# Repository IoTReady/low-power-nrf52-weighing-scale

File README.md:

# Smart Weighing Scale  

This project describes a Smart Weighing Scale with low current consumption, and hence a long battery backup.

One of the biggest problems with the use of weighing scales in flexible retail or industrial applications is the need to provide a source of power to a scale. This causes problems such as safety hazards with a corded scale, inflexibility of placement since the location of power sources limits where the scale can be placed, and finally the inability to function when there is a power interruption. This design eliminates these disadvanteges.

## Firmware
After cloning or downloading this repo find the firmware documentation here "weighing_scale_nrf/firmware/bootloader/documentation/index.html".

## Circuit

### Power Supply
The nrf Based Weighing Scale operates on 3.3V, and is powered by a 3.7V Li-ion battery.
We use a p-MOSFET(IRLML6401) for reverse polarity protection, and a LDO(Low Drop Out) Regulator(TPS7A0233PDBV) to get a stable 3.3V output supply.

### Battery Charging
We use a Li-ion/Li-polymer linear battery charger IC(BQ21040) for charging the battery via a micro-USB outlet. The led indicator stops glowing when the battery is fully charged.

### nRF Module

We are using the MDBT42Q nRF52840 based module as our main MCU and BLE module. It is a very low current consuming and high performance module.
It needs a 3.3V power supply, and we are using its internal DC/DC regulator which is set by connecting a 10uH and 18nH inductor at DCC and DEC4 pins as shown here. We also use an external 32.768 kHz external crystal. For programming this module we need a Segger JLink Debugger, which is available as a separate device or one could use an on-board debugger from any of the Nordic Dev-boards like PCA400, etc...
We kept a few GPIOs out for future use or if need to integrate anything else with the weighing scale.

To measure the battery level we use this voltage divider circuit and measure it use the on board ADC pins.

Tare Button is a push button for using the tare functionality. It basically resets the displayed weight on scale back to zero. The Tare button can also be used to measure multiple items in the same container. Simply add you first item, note the weight, press Tare and you are ready to weigh your next item.

### ADC Circuit: HX711

For measuring the weighing scale we use a Load Cell which gives an anlog output, as the weight changes. For high accuracy we use HX711 24-bit ADC chip, which is designed specifically for industrial weighing scales and other industrial control applications.

To power the HX711 we need a 5V supply, so we use a Boost regulator(LM2703) to step-up the 3.7V from the battery supply and use an LDO(LP2985-5.0) to get a stable noise free 5V supply for HX711.

The data from the Load Cell is received via four pins HX711_IN+, HX711_IN-, HX711_AVDD and GND. This data is processed by the ADC chip and an output is send via serial interface to the nRF module. We can control the output data rate as either 10Hz or 80Hz by controlling the HX711_RATE pin state.
There is no programming needed for the internal registers. All controls to the HX711 are through the pins.

### E-Ink Display

We decided to go with an E-Ink display as it is very low power consuming, reflection resistant, and was useful for the application we were targeting.
This is a 1.54" 200x200 pixel [E-Ink display](https://www.e-paper-display.com/products_detail/productId=513.html) from Good Display.

## PCB
This is what the final PCB design looks like:

## Hardware Builds

Hardware design files are available in the "design" sub-folder

We tried 3 different designs for the weighing scale project and settled with the "HX711" based design as our final.

So you will find the final design explained on the main page.

The other two designs of "LPV821" and "LTC6915" based weighing scales are also fully functional, one may have to play around with the adc functions in the firmware though.

## Software Builds

One can find the main application with all library files(for e-ink display, and weighing scale) in the "Application" folder.

To setup the Nordic SDK and bootloader files follow the links in "Bootloader" folder. Also, the "documentation" folder has some good technical data.

To make changes in the firmware go to "weighing_scale_nrf/firmware/application/w_scale_all/" and make necessary changes.

To build the output files, go to the same location and use this command to generate final output files(.hex):
```
make release
```

Then use the following to flash and debug the firmware:
```
make upload
```

This is a custom makefile, so make sure all Debugger setings are proper. Like, make sure the Debugge name and Serial Number are correct.

These can be set in this [makefile](https://github.com/IoTReady/weighing_scale_nrf/blob/master/firmware/application/w_scale_all/Makefile).

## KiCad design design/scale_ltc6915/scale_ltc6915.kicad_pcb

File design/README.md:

Here one can find all the Hardware design files.
We tried 3 different designs for the weighing scale project and settled with the "HX711" based design as our final.
So you will find the final design explained on the main page.
The other two designs of "LPV821" and "LTC6915" based weighing scales are also fully functional, one may have to play around with the adc functions in the firmware though.

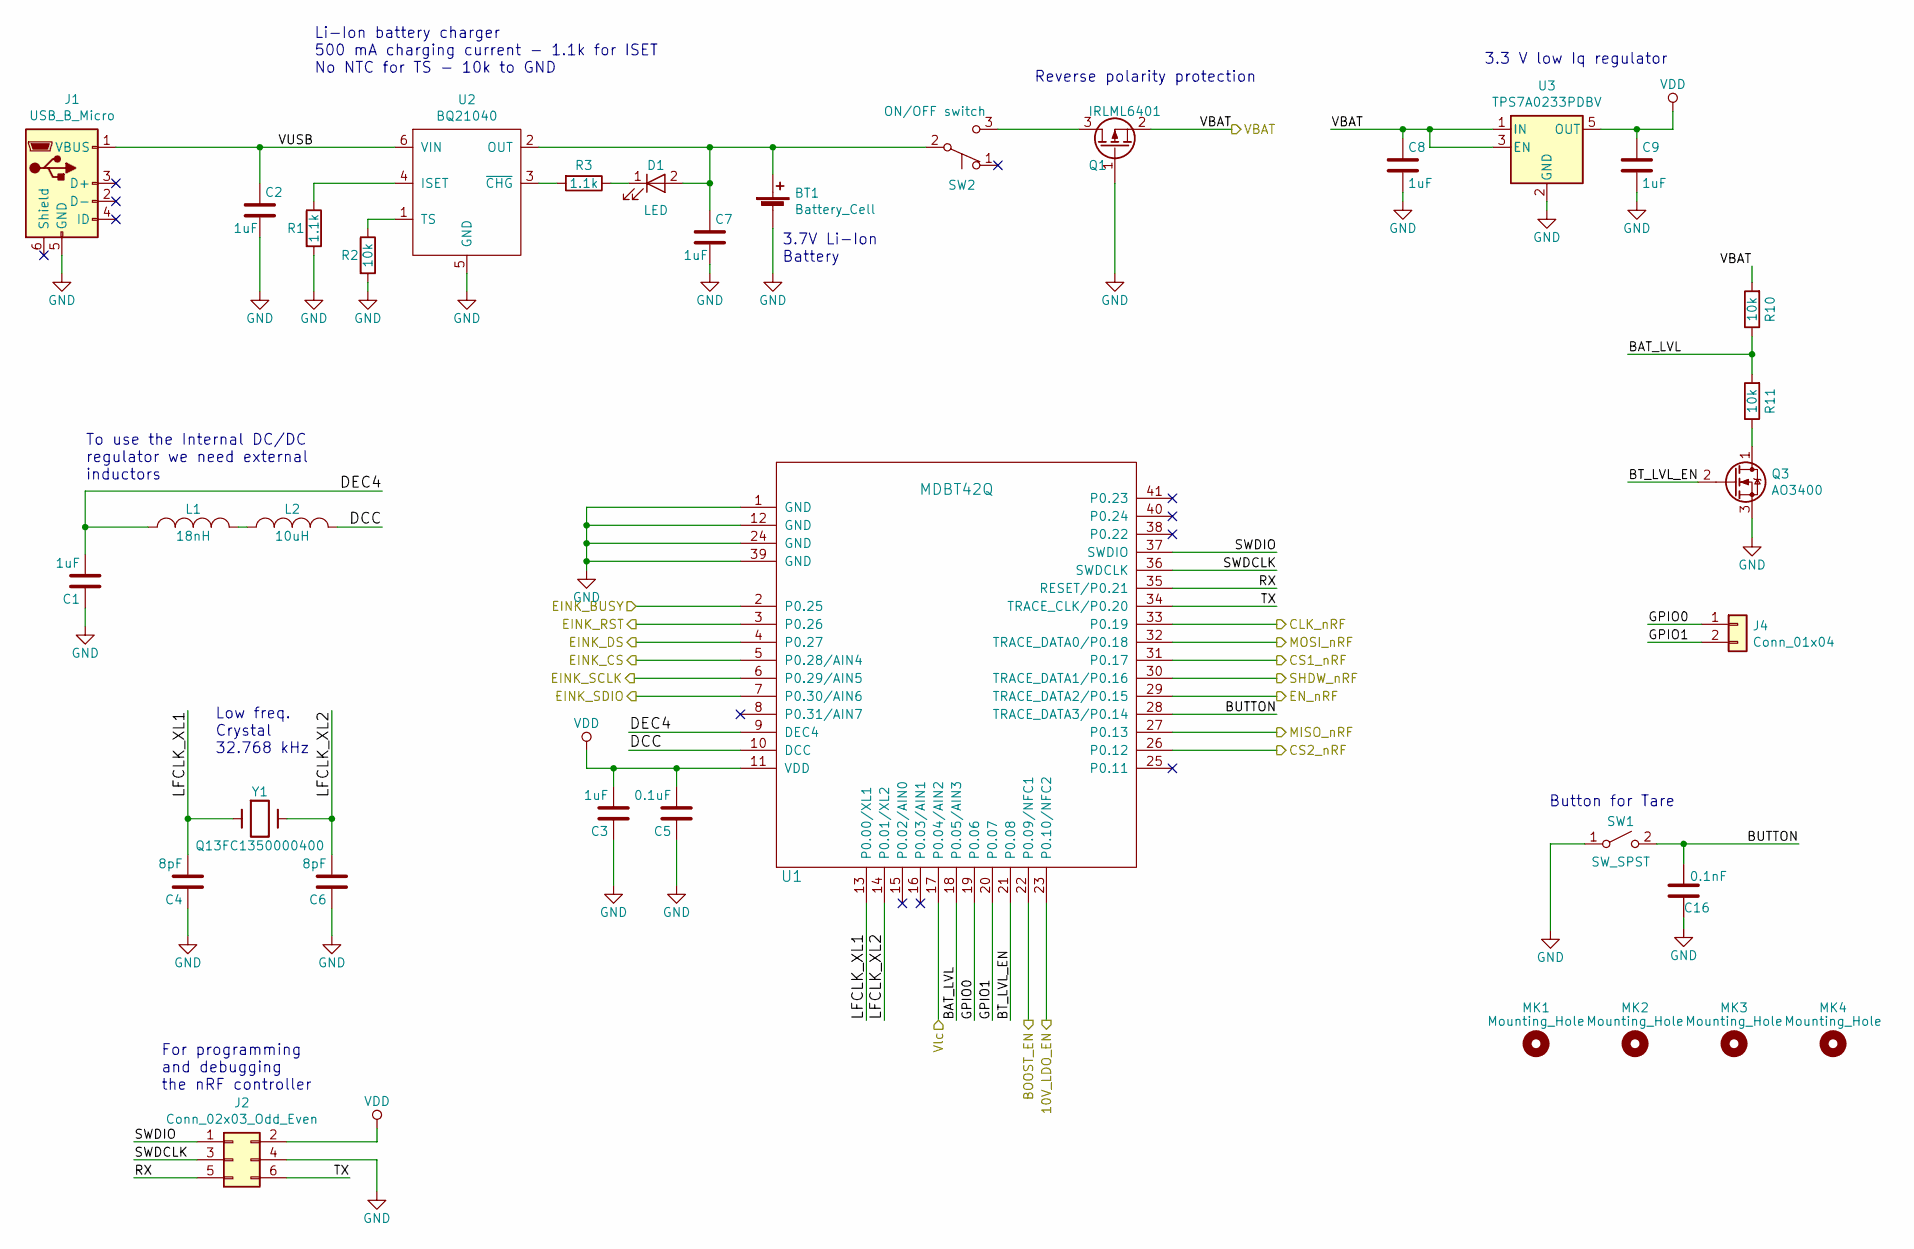
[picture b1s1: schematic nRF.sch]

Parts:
BT1: Battery_Cell; JST_PH_B2B-PH-K_1x02_P2.00mm_Vertical
C1, C3: 1uF; C_0603_1608Metric
C2, C7, C8, C9: 1uF; C_1206_3216Metric
C4, C6: 8pF; C_0402_1005Metric
C5: 0.1uF; C_0402_1005Metric
C16: 0.1nF; C_0402_1005Metric
D1: LED; LED_0603_1608Metric_Castellated
J1: USB_B_Micro; Micro_usb_connector_4_THT_pads
J2: Conn_02x03_Odd_Even; PinHeader_2x03_P2.00mm_Vertical
J4: Conn_01x04; PinHeader_1x02_P2.00mm_Vertical
L1: 18nH; C_0603_1608Metric
L2: 10uH; L_0805
MK1, MK2, MK3, MK4: Mounting_Hole; MountingHole_2.7mm_M2.5
Q1: IRLML6401; SOT-23
Q3: AO3400; SOT-23
R1, R3: 1.1k; R_0603_1608Metric_Pad1.05x0.95mm_HandSolder
R2, R10, R11: 10k; R_0603_1608Metric_Pad1.05x0.95mm_HandSolder
SW1: SW_SPST; SMD Tactile Switch_3x6x2.5mm
SW2: ON/OFF switch; Slide Switch SMD 2P2T _6pins
U1: MDBT42Q; mdbt42Q
U2: BQ21040; SOT-23-6_Handsoldering
U3: TPS7A0233PDBV; SOT-23-5
Y1: Q13FC1350000400; Q13FC1350000400_SMD Crystals 32.768KHz

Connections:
/Sheet5E60241E/EINK_BUSY: U1.2 (P0.25); also elsewhere on the board
/Sheet5E60241E/EINK_CS: U1.5 (P0.28/AIN4); also elsewhere on the board
/Sheet5E60241E/EINK_DS: U1.4 (P0.27); also elsewhere on the board
/Sheet5E60241E/EINK_RST: U1.3 (P0.26); also elsewhere on the board
/Sheet5E60241E/EINK_SCLK: U1.6 (P0.29/AIN5); also elsewhere on the board
/Sheet5E60241E/EINK_SDIO: U1.7 (P0.30/AIN6); also elsewhere on the board
/Sheet5E602498/10V_LDO_EN: U1.23 (P0.10/NFC2); also elsewhere on the board
/Sheet5E602498/BOOST_EN: U1.22 (P0.09/NFC1); also elsewhere on the board
/Sheet5E602498/CLK_nRF: U1.33 (P0.19); also elsewhere on the board
/Sheet5E602498/CS1_nRF: U1.31 (P0.17); also elsewhere on the board
/Sheet5E602498/CS2_nRF: U1.26 (P0.12); also elsewhere on the board
/Sheet5E602498/EN_nRF: U1.29 (TRACE_DATA2/P0.15); also elsewhere on the board
/Sheet5E602498/MISO_nRF: U1.27 (P0.13); also elsewhere on the board
/Sheet5E602498/MOSI_nRF: U1.32 (TRACE_DATA0/P0.18); also elsewhere on the board
/Sheet5E602498/SHDW_nRF: U1.30 (TRACE_DATA1/P0.16); also elsewhere on the board
/Sheet5E602498/VBAT: C8.1, Q1.2 (G), R10.2, U3.1 (IN), U3.3 (EN); also elsewhere on the board
/Sheet5E602498/Vlc: U1.17 (P0.04/AIN2); also elsewhere on the board
/nRF/BAT_LVL: R10.1, R11.2, U1.18 (P0.05/AIN3)
/nRF/BT_LVL_EN: Q3.2 (G), U1.21 (P0.08)
/nRF/BUTTON: C16.2, SW1.2 (B), U1.28 (TRACE_DATA3/P0.14)
/nRF/DCC: L2.2, U1.10 (DCC)
/nRF/DEC4: C1.2, L1.1, U1.9 (DEC4)
/nRF/GPIO0: J4.1, U1.19 (P0.06)
/nRF/GPIO1: J4.2, U1.20 (P0.07)
/nRF/LFCLK_XL1: C4.2, U1.13 (P0.00/XL1), Y1.1
/nRF/LFCLK_XL2: C6.2, U1.14 (P0.01/XL2), Y1.2
/nRF/RX: J2.5, U1.35 (RESET/P0.21)
/nRF/SWDCLK: J2.3, U1.36 (SWDCLK)
/nRF/SWDIO: J2.1, U1.37 (SWDIO)
/nRF/TX: J2.6, U1.34 (TRACE_CLK/P0.20)
/nRF/VUSB: C2.1, J1.1 (VBUS), U2.6 (VIN)
GND: BT1.2, C1.1, C2.2, C3.1, C4.1, C5.1, C6.1, C7.2, C8.2, C9.2, C16.1, J1.5 (GND), J2.4, Q1.1 (D), Q3.3 (S), R1.2, R2.2, SW1.1 (A), U1.1 (GND), U1.12 (GND), U1.24 (GND), U1.39 (GND), U2.5 (GND), U3.2 (GND); also elsewhere on the board
unnamed: BT1.1, C7.1, D1.2 (A), SW2.2 (B), U2.2 (OUT)
unnamed: D1.1 (K), R3.1
unnamed: L1.2, L2.1
unnamed: Q1.3 (S), SW2.3 (C)
unnamed: Q3.1 (D), R11.1
unnamed: R1.1, U2.4 (ISET)
unnamed: R2.1, U2.1 (TS)
unnamed: R3.2, U2.3 (~CHG)
VDD: C3.2, C5.2, C9.1, J2.2, U1.11 (VDD), U3.5 (OUT); also elsewhere on the board

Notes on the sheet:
3.7V Li-Ion Battery
Reverse polarity protection
Button for Tare
To use the Internal DC/DC regulator we need external inductors
For programming and debugging the nRF controller
Low freq. Crystal 32.768 kHz
3.3 V low Iq regulator
Li-Ion battery charger 500 mA charging current - 1.1k for ISET No NTC for TS - 10k to GND

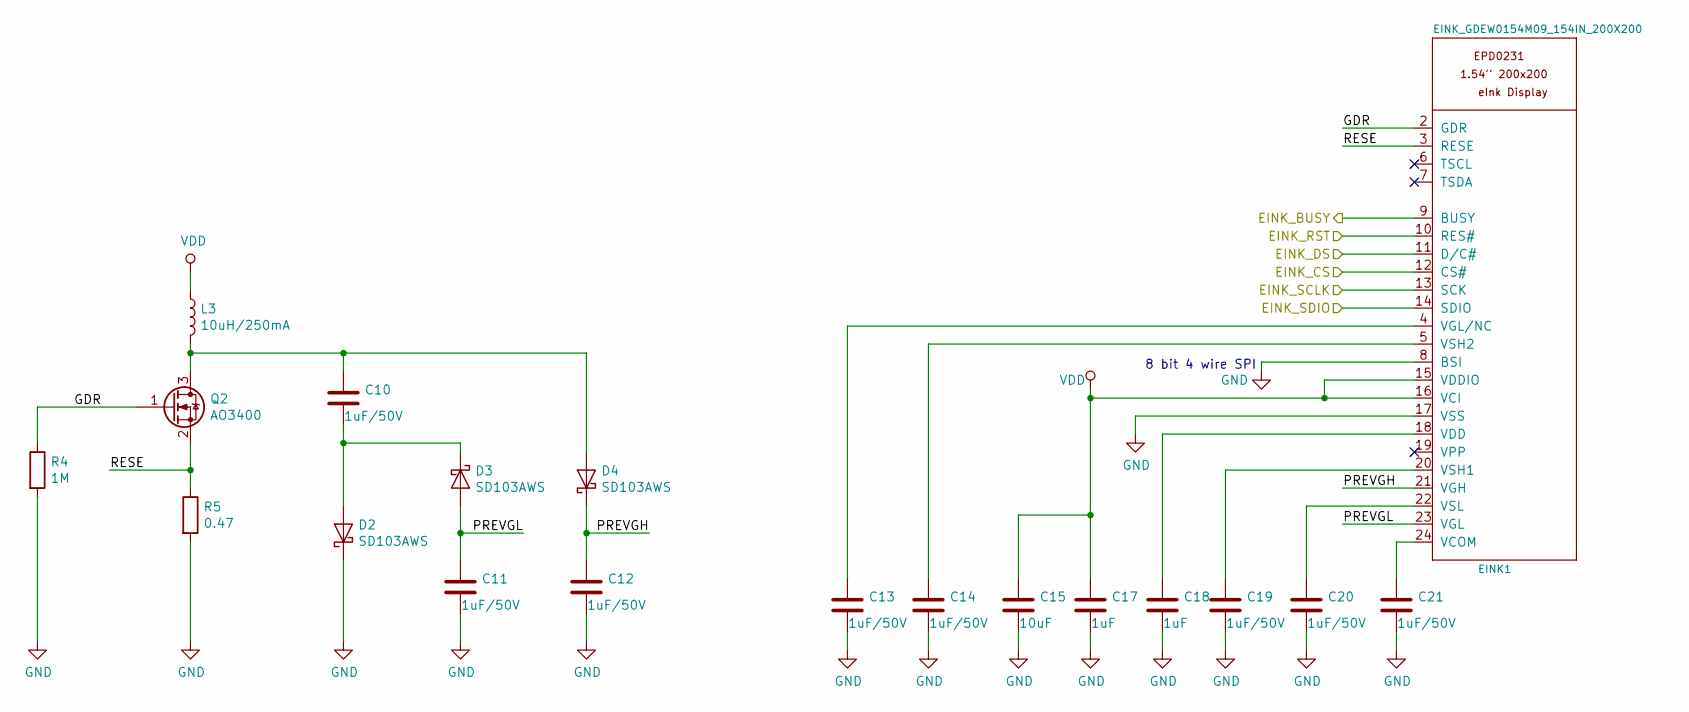
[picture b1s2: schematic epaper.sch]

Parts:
C10, C11, C12, C13, C14, C19, C20, C21: 1uF/50V; C_0603_1608Metric_Pad1.05x0.95mm_HandSolder
C15: 10uF; C_0603_1608Metric_Pad1.05x0.95mm_HandSolder
C17, C18: 1uF; C_0603_1608Metric_Pad1.05x0.95mm_HandSolder
D2, D3, D4: SD103AWS; D_SOD-323_HandSoldering
EINK1: EINK_GDEW0154M09_154IN_200X200; Hirose_FH12-24S-0.5SH_1x24-1MP_P0.50mm_Horizontal
L3: 10uH/250mA; L_3.5x3.0mm_CD30D22
Q2: AO3400; SOT-23
R4: 1M; R_0603_1608Metric_Pad1.05x0.95mm_HandSolder
R5: 0.47; R_1206_3216Metric

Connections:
/Sheet5E60241E/EINK_BUSY: EINK1.9 (BUSY); also elsewhere on the board
/Sheet5E60241E/EINK_CS: EINK1.12 (CS#); also elsewhere on the board
/Sheet5E60241E/EINK_DS: EINK1.11 (D/C#); also elsewhere on the board
/Sheet5E60241E/EINK_RST: EINK1.10 (RES#); also elsewhere on the board
/Sheet5E60241E/EINK_SCLK: EINK1.13 (SCK); also elsewhere on the board
/Sheet5E60241E/EINK_SDIO: EINK1.14 (SDIO); also elsewhere on the board
/Sheet5E60241E/GDR: EINK1.2 (GDR), Q2.1 (G), R4.1
/Sheet5E60241E/PREVGH: C12.1, D4.1 (K), EINK1.21 (VGH)
/Sheet5E60241E/PREVGL: C11.1, D3.2 (A), EINK1.23 (VGL)
/Sheet5E60241E/RESE: EINK1.3 (RESE), Q2.2 (S), R5.1
GND: C11.2, C12.2, C13.2, C14.2, C15.2, C17.2, C18.2, C19.2, C20.2, C21.2, D2.1 (K), EINK1.8 (BSI), EINK1.17 (VSS), R4.2, R5.2; also elsewhere on the board
unnamed: C10.1, D4.2 (A), L3.2, Q2.3 (D)
unnamed: C10.2, D2.2 (A), D3.1 (K)
unnamed: C13.1, EINK1.4 (VGL/NC)
unnamed: C14.1, EINK1.5 (VSH2)
unnamed: C18.1, EINK1.18 (VDD)
unnamed: C19.1, EINK1.20 (VSH1)
unnamed: C20.1, EINK1.22 (VSL)
unnamed: C21.1, EINK1.24 (VCOM)
VDD: C15.1, C17.1, EINK1.15 (VDDIO), EINK1.16 (VCI), L3.1; also elsewhere on the board

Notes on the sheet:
8 bit 4 wire SPI

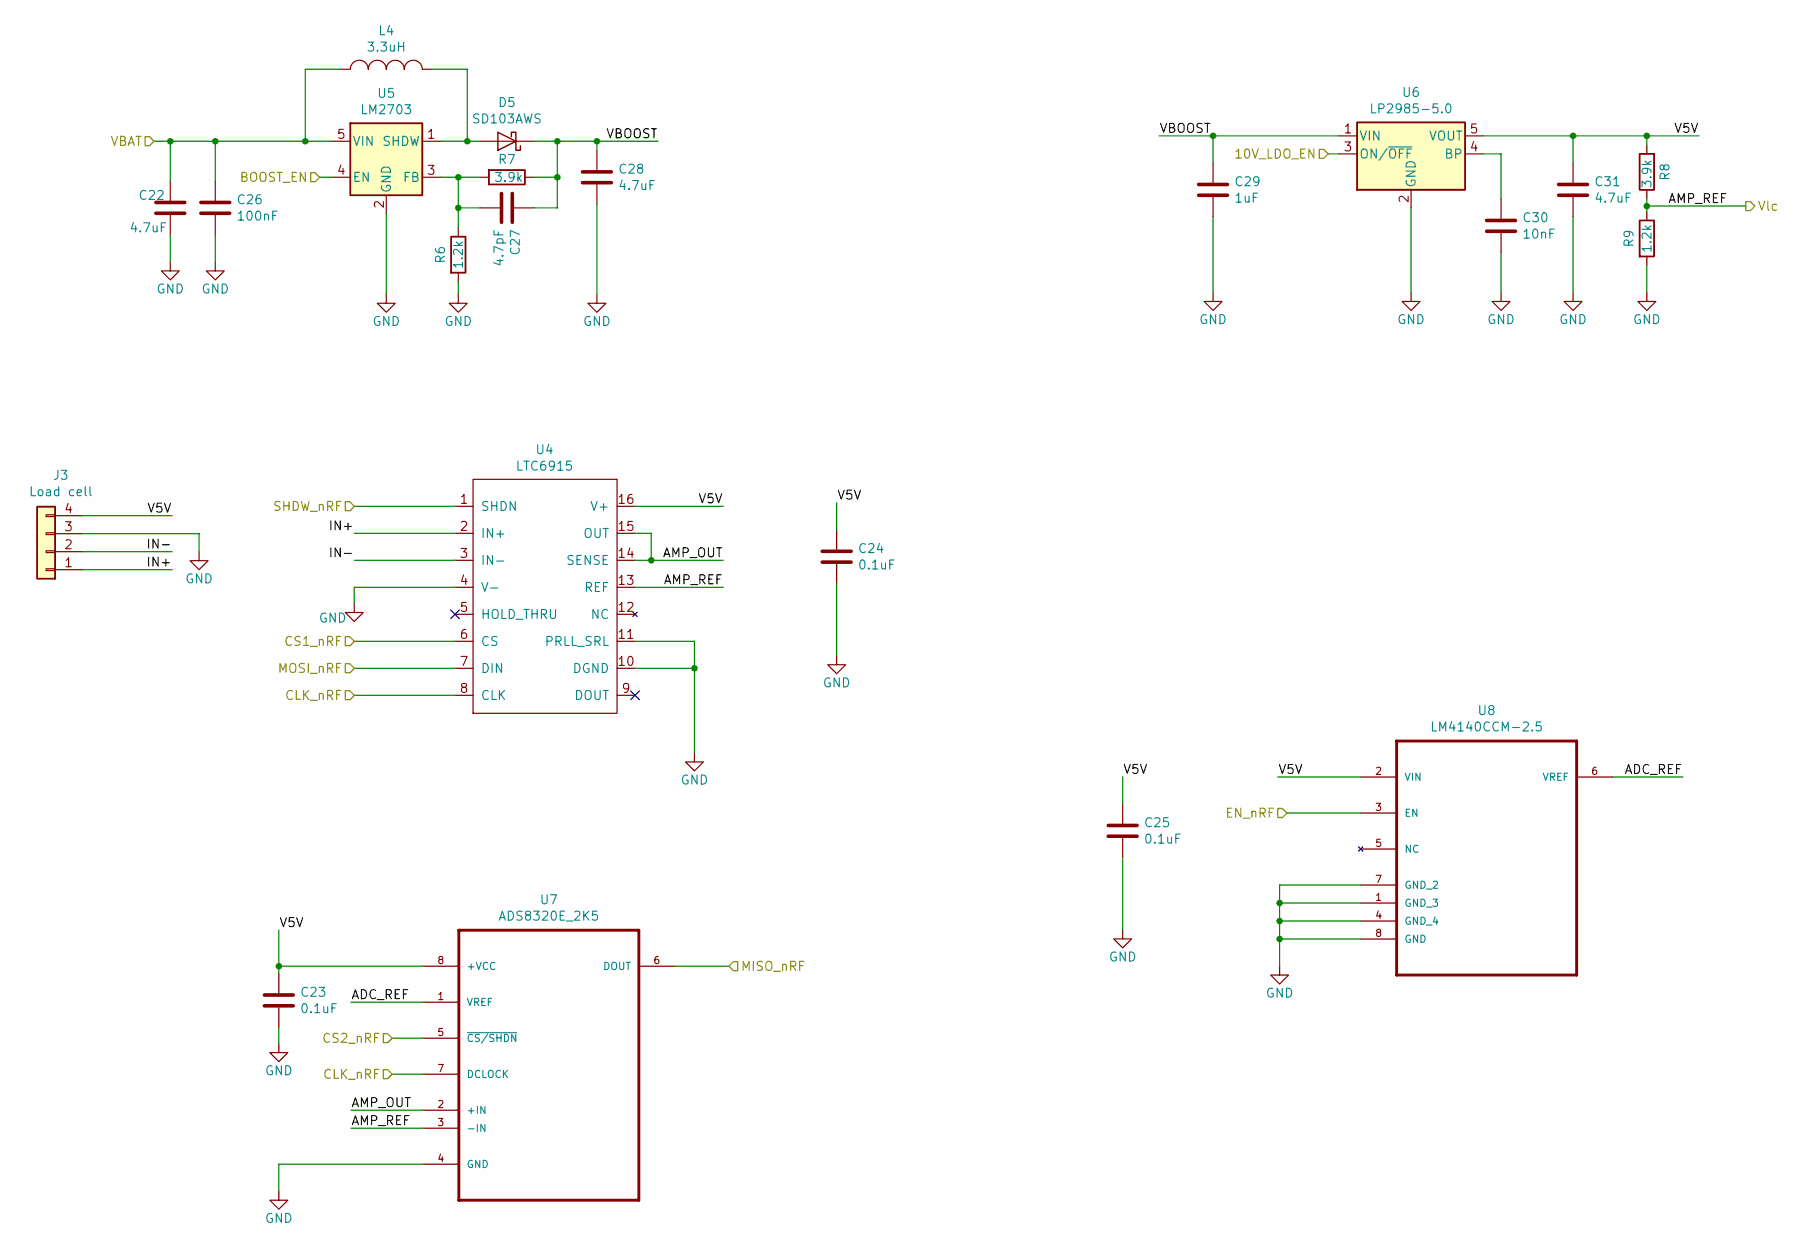
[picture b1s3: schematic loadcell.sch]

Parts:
C22, C28, C31: 4.7uF; C_0603_1608Metric_Pad1.05x0.95mm_HandSolder
C23, C24, C25: 0.1uF; C_0603_1608Metric_Pad1.05x0.95mm_HandSolder
C26: 100nF; C_0603_1608Metric_Pad1.05x0.95mm_HandSolder
C27: 4.7pF; C_0603_1608Metric_Pad1.05x0.95mm_HandSolder
C29: 1uF; C_0603_1608Metric_Pad1.05x0.95mm_HandSolder
C30: 10nF; C_0603_1608Metric_Pad1.05x0.95mm_HandSolder
D5: SD103AWS; D_SOD-323_HandSoldering
J3: Load cell; JST_PH_B4B-PH-K_1x04_P2.00mm_Vertical
L4: 3.3uH; L_3.5x3.0mm_CD30D22
R6, R9: 1.2k; R_0603_1608Metric_Pad1.05x0.95mm_HandSolder
R7, R8: 3.9k; R_0603_1608Metric_Pad1.05x0.95mm_HandSolder
U4: LTC6915; SSOP-16_3.9x4.9mm_P0.635mm
U5: LM2703; SOT-23-5
U6: LP2985-5.0; SOT-23-5
U7: ADS8320E_2K5; VSSOP-8_3.0x3.0mm_P0.65mm
U8: LM4140CCM-2.5; SOIC-8_3.9x4.9mm_P1.27mm

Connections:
/Sheet5E602498/10V_LDO_EN: U6.3 (ON/~OFF~); also elsewhere on the board
/Sheet5E602498/ADC_REF: U7.1 (VREF), U8.6 (VREF)
/Sheet5E602498/AMP_OUT: U4.14 (SENSE), U4.15 (OUT), U7.2 (+IN)
/Sheet5E602498/BOOST_EN: U5.4 (EN); also elsewhere on the board
/Sheet5E602498/CLK_nRF: U4.8 (CLK), U7.7 (DCLOCK); also elsewhere on the board
/Sheet5E602498/CS1_nRF: U4.6 (CS); also elsewhere on the board
/Sheet5E602498/CS2_nRF: U7.5 (~CS/SHDN); also elsewhere on the board
/Sheet5E602498/EN_nRF: U8.3 (EN); also elsewhere on the board
/Sheet5E602498/IN+: J3.1, U4.2 (IN+)
/Sheet5E602498/IN-: J3.2, U4.3 (IN-)
/Sheet5E602498/MISO_nRF: U7.6 (DOUT); also elsewhere on the board
/Sheet5E602498/MOSI_nRF: U4.7 (DIN); also elsewhere on the board
/Sheet5E602498/SHDW_nRF: U4.1 (SHDN); also elsewhere on the board
/Sheet5E602498/V5V: C23.1, C24.1, C25.1, C31.1, J3.4, R8.2, U4.16 (V+), U6.5 (VOUT), U7.8 (+VCC), U8.2 (VIN)
/Sheet5E602498/VBAT: C22.1, C26.1, L4.1, U5.5 (VIN); also elsewhere on the board
/Sheet5E602498/VBOOST: C27.1, C28.1, C29.1, D5.1 (K), R7.1, U6.1 (VIN)
/Sheet5E602498/Vlc: R8.1, R9.1, U4.13 (REF), U7.3 (-IN); also elsewhere on the board
GND: C22.2, C23.2, C24.2, C25.2, C26.2, C28.2, C29.2, C30.2, C31.2, J3.3, R6.2, R9.2, U4.4 (V-), U4.10 (DGND), U4.11 (PRLL_SRL), U5.2 (GND), U6.2 (GND), U7.4 (GND), U8.1 (GND_3), U8.4 (GND_4), U8.7 (GND_2), U8.8 (GND); also elsewhere on the board
unnamed: C27.2, R6.1, R7.2, U5.3 (FB)
unnamed: C30.1, U6.4 (BP)
unnamed: D5.2 (A), L4.2, U5.1 (SHDW)

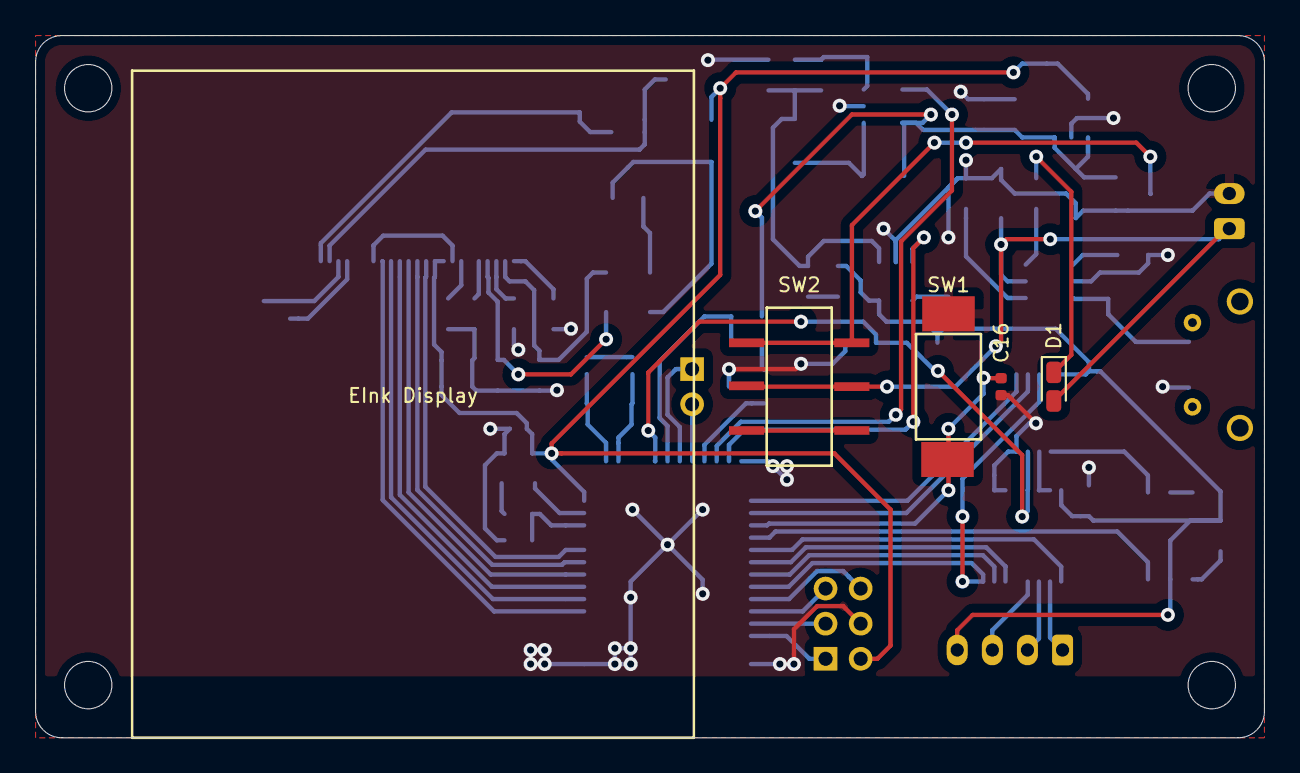
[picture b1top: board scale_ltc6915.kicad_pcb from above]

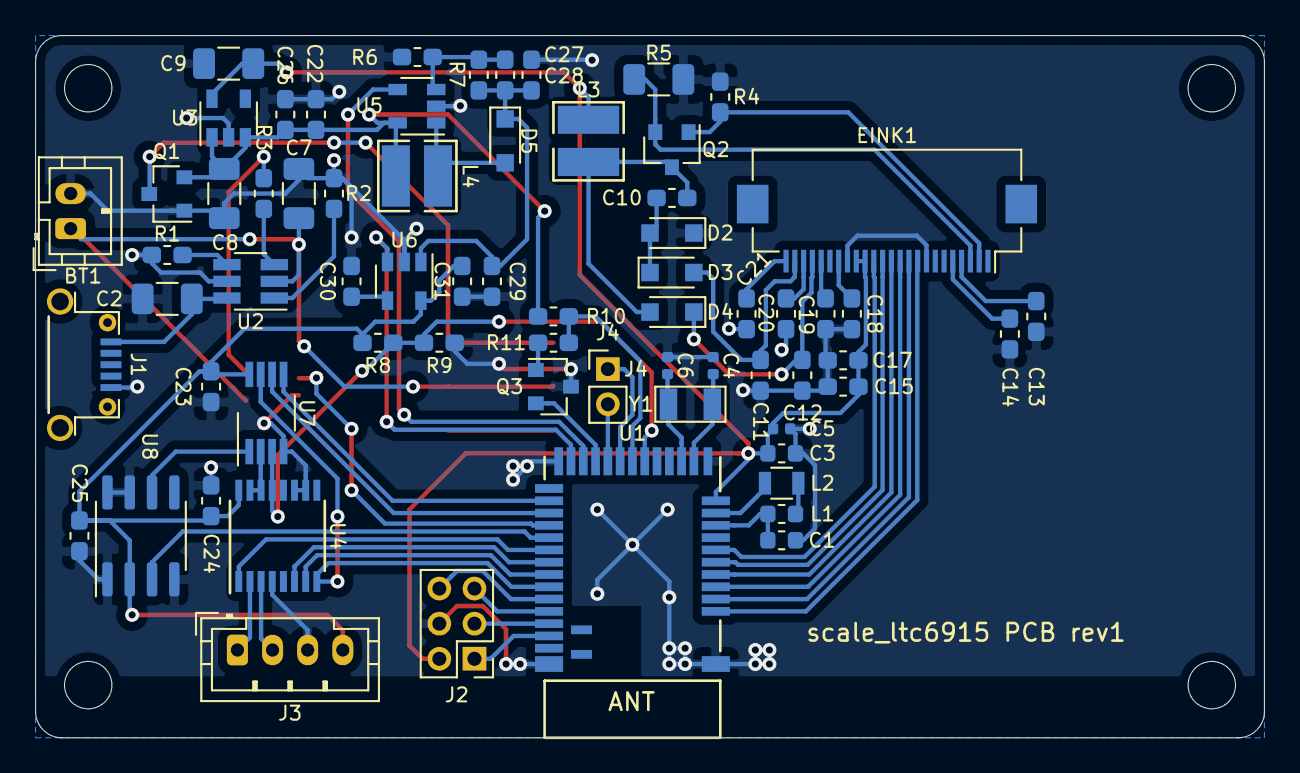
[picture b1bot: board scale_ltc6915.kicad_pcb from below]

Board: 2 copper layers, 70.0 x 40.0 mm, 76 parts (67 on the bottom side), 62 nets.

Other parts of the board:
EInk Display: 1.54inch_EInk_display

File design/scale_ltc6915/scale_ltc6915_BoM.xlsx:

Source: | /home/shubham/IoTReady/nrf_scale/weighing_scale_nrf/design/scale_ltc6915/scale_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
Date: | Fri Mar 6 21:35:52 2020
Tool: | Eeschema 5.1.5-52549c5~84~ubuntu18.04.1
Component Count: | 73
Ref | Value | Footprint | Datasheet | Manufacturer | Vendor
BT1 | Battery_Cell | Connector_JST:JST_PH_B2B-PH-K_1x02_P2.00mm_Vertical
C1 | 1uF | sense_fp:C_0603_1608Metric
C2 | 1uF | sense_fp:C_1206_3216Metric
C3 | 1uF | sense_fp:C_0603_1608Metric
C4 | 8pF | sense_fp:C_0402_1005Metric
C5 | 0.1uF | sense_fp:C_0402_1005Metric
C6 | 8pF | sense_fp:C_0402_1005Metric
C7 | 1uF | sense_fp:C_1206_3216Metric
C8 | 1uF | sense_fp:C_1206_3216Metric
C9 | 1uF | sense_fp:C_1206_3216Metric
C10 | 1uF/50V | Capacitor_SMD:C_0603_1608Metric_Pad1.05x0.95mm_HandSolder
C11 | 1uF/50V | Capacitor_SMD:C_0603_1608Metric_Pad1.05x0.95mm_HandSolder
C12 | 1uF/50V | Capacitor_SMD:C_0603_1608Metric_Pad1.05x0.95mm_HandSolder
C13 | 1uF/50V | Capacitor_SMD:C_0603_1608Metric_Pad1.05x0.95mm_HandSolder
C14 | 1uF/50V | Capacitor_SMD:C_0603_1608Metric_Pad1.05x0.95mm_HandSolder
C15 | 10uF | Capacitor_SMD:C_0603_1608Metric_Pad1.05x0.95mm_HandSolder
C16 | 0.1nF | sense_fp:C_0402_1005Metric
C17 | 1uF | Capacitor_SMD:C_0603_1608Metric_Pad1.05x0.95mm_HandSolder
C18 | 1uF | Capacitor_SMD:C_0603_1608Metric_Pad1.05x0.95mm_HandSolder
C19 | 1uF/50V | Capacitor_SMD:C_0603_1608Metric_Pad1.05x0.95mm_HandSolder
C20 | 1uF/50V | Capacitor_SMD:C_0603_1608Metric_Pad1.05x0.95mm_HandSolder
C21 | 1uF/50V | Capacitor_SMD:C_0603_1608Metric_Pad1.05x0.95mm_HandSolder
C22 | 4.7uF | Capacitor_SMD:C_0603_1608Metric_Pad1.05x0.95mm_HandSolder | ~
C23 | 0.1uF | Capacitor_SMD:C_0603_1608Metric_Pad1.05x0.95mm_HandSolder | ~
C24 | 0.1uF | Capacitor_SMD:C_0603_1608Metric_Pad1.05x0.95mm_HandSolder | ~
C25 | 0.1uF | Capacitor_SMD:C_0603_1608Metric_Pad1.05x0.95mm_HandSolder | ~
C27 | 100nF | Capacitor_SMD:C_0603_1608Metric_Pad1.05x0.95mm_HandSolder | ~
C28 | 4.7pF | Capacitor_SMD:C_0603_1608Metric_Pad1.05x0.95mm_HandSolder | ~
C29 | 4.7uF | Capacitor_SMD:C_0603_1608Metric_Pad1.05x0.95mm_HandSolder | ~
C30 | 1uF | Capacitor_SMD:C_0603_1608Metric_Pad1.05x0.95mm_HandSolder | ~
C31 | 10nF | Capacitor_SMD:C_0603_1608Metric_Pad1.05x0.95mm_HandSolder | ~
C32 | 4.7uF | Capacitor_SMD:C_0603_1608Metric_Pad1.05x0.95mm_HandSolder | ~
D1 | LED | LED_SMD:LED_0603_1608Metric_Castellated
D2 | SD103AWS | Diode_SMD:D_SOD-323_HandSoldering | ~
D3 | SD103AWS | Diode_SMD:D_SOD-323_HandSoldering | ~
D4 | SD103AWS | Diode_SMD:D_SOD-323_HandSoldering | ~
D5 | SD103AWS | Diode_SMD:D_SOD-323_HandSoldering | ~
EINK1 | EINK_GDEW0154M09_154IN_200X200 | Connector_FFC-FPC:Hirose_FH12-24S-0.5SH_1x24-1MP_P0.50mm_Horizontal
J1 | USB_B_Micro | Footprint_nrf_scale:Micro_usb_connector_4_THT_pads | ~
J2 | Conn_02x03_Odd_Even | Connector_PinHeader_2.00mm:PinHeader_2x03_P2.00mm_Vertical | ~
J3 | Load cell | Connector_JST:JST_PH_B4B-PH-K_1x04_P2.00mm_Vertical
L1 | 18nH | sense_fp:C_0603_1608Metric
L2 | 10uH | sense_fp:L_0805
L3 | 10uH/250mA | Footprint_nrf_scale:L_3.5x3.0mm_CD30D22
L4 | 3.3uH | Footprint_nrf_scale:L_3.5x3.0mm_CD30D22
MK1 | Mounting_Hole | sense_fp:MountingHole_2.7mm_M2.5
MK2 | Mounting_Hole | sense_fp:MountingHole_2.7mm_M2.5
MK3 | Mounting_Hole | sense_fp:MountingHole_2.7mm_M2.5
MK4 | Mounting_Hole | sense_fp:MountingHole_2.7mm_M2.5
Q1 | IRLML6401 | Package_TO_SOT_SMD:SOT-23
Q2 | AO3400 | Package_TO_SOT_SMD:SOT-23
R1 | 1.1k | Resistor_SMD:R_0603_1608Metric_Pad1.05x0.95mm_HandSolder
R2 | 10k | Resistor_SMD:R_0603_1608Metric_Pad1.05x0.95mm_HandSolder
R3 | 1.1k | Resistor_SMD:R_0603_1608Metric_Pad1.05x0.95mm_HandSolder
R4 | 1M | Resistor_SMD:R_0603_1608Metric_Pad1.05x0.95mm_HandSolder
R5 | 0.47 | Resistor_SMD:R_0603_1608Metric_Pad1.05x0.95mm_HandSolder
R6 | 3.9k | Resistor_SMD:R_0603_1608Metric_Pad1.05x0.95mm_HandSolder
R7 | 1.2k | Resistor_SMD:R_0603_1608Metric_Pad1.05x0.95mm_HandSolder
R10 | 1.2k | Resistor_SMD:R_0603_1608Metric_Pad1.05x0.95mm_HandSolder
R11 | 3.9k | Resistor_SMD:R_0603_1608Metric_Pad1.05x0.95mm_HandSolder
R12 | 3.9k | Resistor_SMD:R_0603_1608Metric_Pad1.05x0.95mm_HandSolder
R13 | 1.2k | Resistor_SMD:R_0603_1608Metric_Pad1.05x0.95mm_HandSolder
SW1 | SW_SPST | Footprint_nrf_scale:SMD Tactile Switch_3x6x2.5mm
SW2 | ON/OFF switch | Footprint_nrf_scale:Slide Switch SMD 2P2T _6pins
U1 | MDBT42Q | sense_fp:mdbt42Q
U2 | BQ21040 | Package_TO_SOT_SMD:SOT-23-6_Handsoldering | http://www.ti.com/lit/ds/symlink/bq21040.pdf
U3 | TPS7A0233PDBV | Package_TO_SOT_SMD:SOT-23-5 | http://www.ti.com/lit/ds/symlink/tps7a02.pdf
U4 | LTC6915
U5 | LM2703 | Package_TO_SOT_SMD:SOT-23-5
U6 | LP2985-5.0 | Package_TO_SOT_SMD:SOT-23-5 | http://www.ti.com/lit/ds/symlink/lp2985.pdf
U7 | ADS8320E_2K5 | SOP65P490X110-8N | Texas Instruments
U8 | LM4140CCM-2.5 | SOIC127P600X175-8N | NationalSemiconductor
Y1 | Q13FC1350000400 | sense_fp:Q13FC1350000400_SMD Crystals 32.768KHz

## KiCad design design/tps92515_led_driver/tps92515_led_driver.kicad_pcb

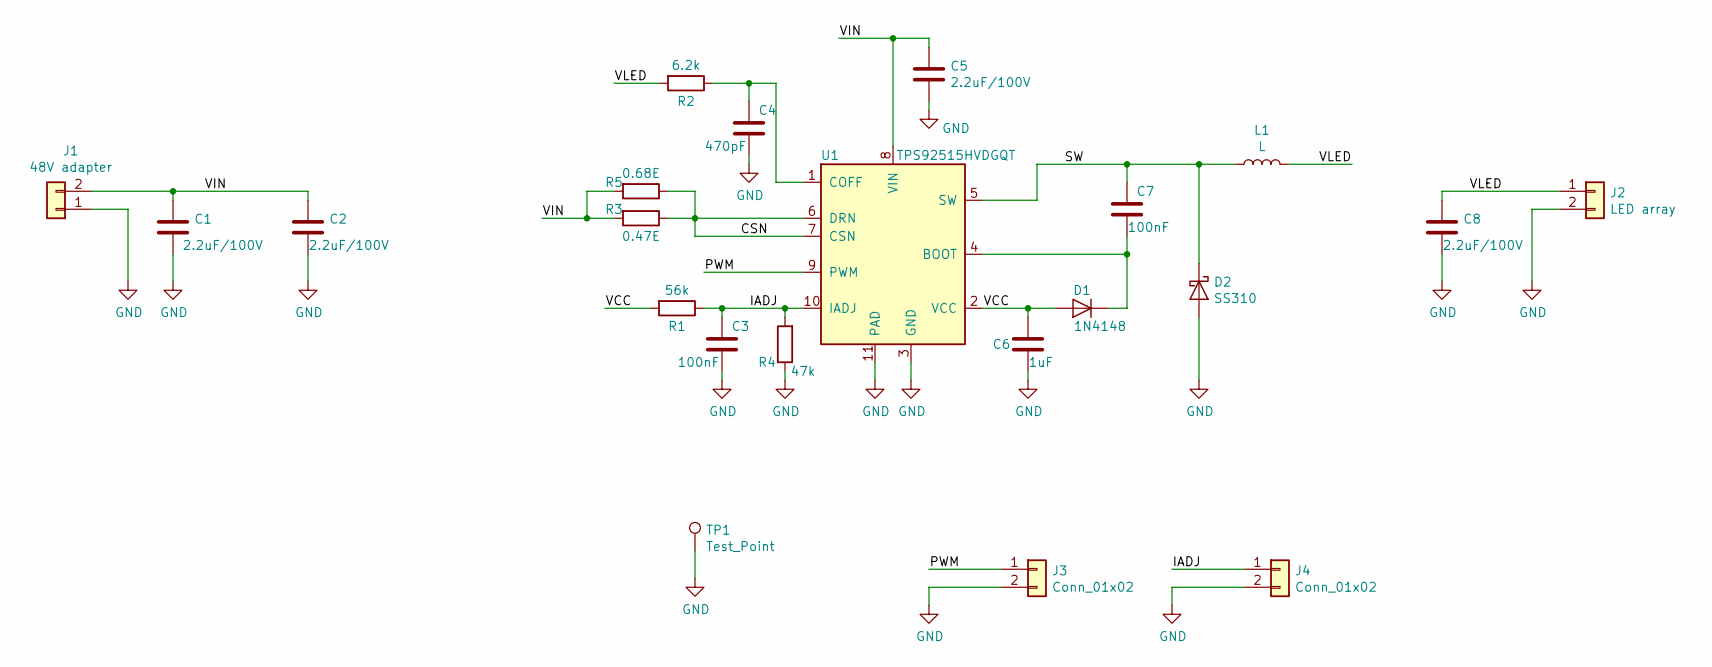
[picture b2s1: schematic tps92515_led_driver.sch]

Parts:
C1, C2, C5, C8: 2.2uF/100V; C_1206_3216Metric
C3, C7: 100nF; C_0603_1608Metric_Pad1.05x0.95mm_HandSolder
C4: 470pF; C_0603_1608Metric_Pad1.05x0.95mm_HandSolder
C6: 1uF; C_0603_1608Metric_Pad1.05x0.95mm_HandSolder
D1: 1N4148; D_SOD-523
D2: SS310; D_SMB
J1: 48V adapter; TerminalBlock_bornier-2_P5.08mm
J2: LED array; TerminalBlock_bornier-2_P5.08mm
J3, J4: Conn_01x02; PinHeader_1x02_P2.54mm_Vertical
L1: L; L_Abracon_ASPI-0630LR
R1: 56k; C_1206_3216Metric
R2: 6.2k; C_0603_1608Metric_Pad1.05x0.95mm_HandSolder
R3: 0.47E; R_1206_3216Metric_Pad1.42x1.75mm_HandSolder
R4: 47k; C_1206_3216Metric
R5: 0.68E; R_1206_3216Metric_Pad1.42x1.75mm_HandSolder
TP1: Test_Point; PinHeader_1x01_P2.54mm_Vertical
U1: TPS92515HVDGQT; MSOP-10-1EP_3x3mm_P0.5mm_EP1.68x1.88mm_ThermalVias

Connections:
/CSN: R3.1, R5.1, U1.6 (DRN), U1.7 (CSN)
/IADJ: C3.1, J4.1, R1.1, R4.2, U1.10 (IADJ)
/PWM: J3.1, U1.9 (PWM)
/SW: C7.1, D2.1 (K), L1.1, U1.5 (SW)
/VCC: C6.1, D1.2 (A), R1.2, U1.2 (VCC)
/VIN: C1.1, C2.1, C5.1, J1.2, R3.2, R5.2, U1.8 (VIN)
/VLED: C8.1, J2.1, L1.2, R2.2
GND: C1.2, C2.2, C3.2, C4.2, C5.2, C6.2, C8.2, D2.2 (A), J1.1, J2.2, J3.2, J4.2, R4.1, TP1.1, U1.3 (GND), U1.11 (PAD); also elsewhere on the board
unnamed: C4.1, R2.1, U1.1 (COFF)
unnamed: C7.2, D1.1 (K), U1.4 (BOOT)

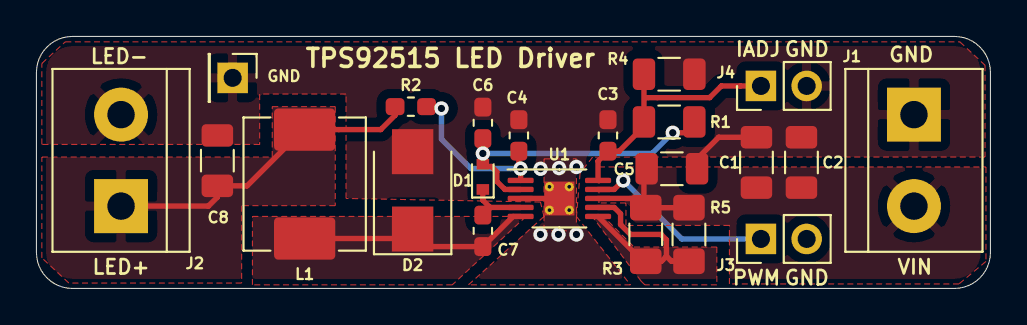
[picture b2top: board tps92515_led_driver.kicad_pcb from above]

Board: 2 copper layers, 53.0 x 14.0 mm, 22 parts (0 on the bottom side), 10 nets.

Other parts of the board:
GND: Test_Point; PinHeader_1x01_P2.54mm_Vertical

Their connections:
GND: GND.1; also elsewhere on the board

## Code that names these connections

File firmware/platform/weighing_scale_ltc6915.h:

/**
 *  pca10040.h : PCA10040 board definitions
 *  Copyright (C) 2019  Appiko
 *
 *  This program is free software: you can redistribute it and/or modify
 *  it under the terms of the GNU General Public License as published by
 *  the Free Software Foundation, either version 3 of the License, or
 *  (at your option) any later version.
 *
 *  This program is distributed in the hope that it will be useful,
 *  but WITHOUT ANY WARRANTY; without even the implied warranty of
 *  MERCHANTABILITY or FITNESS FOR A PARTICULAR PURPOSE.  See the
 *  GNU General Public License for more details.
 *  
 *  You should have received a copy of the GNU General Public License
 *  along with this program.  If not, see <https://www.gnu.org/licenses/>.
 */

/**
 * @addtogroup group_platform
 * @{
 *
 * @defgroup board_pca10040 PCA10040 nRF52-DK
 * @brief The nRF52 Development Kit (DK) platform PCA10040
 * @{
 */

#ifndef PLATFORM_W_SCALE_HX711
#define PLATFORM_W_SCALE_HX711

/** @anchor general-gpio
 * @name General GPIO definitions
 * @{*/
#define GPIO_0          (6)
#define GPIO_1          (7)
/** The output level at which the LEDs shine */
#define LEDS_ACTIVE_STATE (0)
/** @} */

/** @anchor weighing_scale_button
 * @name Button Pins
 * @{*/
#define BUTTON_PIN      (14)
/** The input level when the button is pressed */
#define BUTTONS_ACTIVE_STATE (0)
/** The kind of internal resistors required for the button */
#define BUTTON_PULL     (HAL_GPIO_PULLUP)
/** @} */

/** @anchor weighing_scale_serial_interface
 * @name Serial port definitions for Weighing Scale HX711 board
 * @{*/
#define RX_PIN_NUMBER   (21)
#define TX_PIN_NUMBER   (20)
#define CTS_PIN_NUMBER  (7)
#define RTS_PIN_NUMBER  (5)
/** Bool to say if the hardware flow control is required */
#define HWFC            (false)
/** @} */

/** @anchor e_ink_paper_interface 
 * @name E-Ink Paper display Interface
 * @{*/
#define EINK_BUSY       (25)
#define EINK_RST        (26)
#define EINK_DC         (27)
#define EINK_CS         (28)
#define EINK_SCLK       (29)
#define EINK_MOSI       (30)
#define EINK_MISO       (23) //Unused
/** @} */

/** @anchor amplifier_interface 
 * @name amplifier Interface
 * @{*/
#define AMP_ADC_CLK     (19)
#define AMP_ADC_MOSI    (18)
#define AMP_ADC_MISO    (13)
#define LTC6915_AMP_CS  (17)
#define ADS8320_ADC_CS  (12)
#define LM4140_REF_EN   (15)
#define LTC6915_SHDN    (16)
#define VLC_PIN         (4)
#define LDO_EN          (10)
#define BOOST_EN        (9)
/** @} */

/** @anchor batt_level 
 * @name Battery Level
 * @{*/
#define BT_LV           (5)
#define BT_LV_ANALOG    (ANALOG_PIN_5)
#define BT_LV_EN        (8)
/** @} */

///Bool define if the circuitry is present for the internal DC-DC of nRF52
#define DC_DC_CIRCUITRY     true

///Bool define if a NFC Antenna circuitry is present
#define NFC_CIRCUITRY       false

///Bool define if the 32 kHz crystal is present for the LFCLK
#define LFCLK_XTAL_PRESENT  true

///Bool define if a crystal is present for the HFCLK
#define HFCLK_XTAL_PRESENT  true

/** Low frequency clock source used when initializing the SoftDevice */
#define BOARD_LFCLKSRC_STRUCT  {.source        = NRF_CLOCK_LF_SRC_XTAL,            \
                                    .rc_ctiv       = 0,                                \
                                    .rc_temp_ctiv  = 0,                                \
                                    .accuracy = NRF_CLOCK_LF_ACCURACY_20_PPM}

#define BOARD_LFCLKSRC         NRF_CLOCK_LFCLK_Xtal

#endif /* PLATFORM_W_SCALE_HX711 */

/** @} */
/** @} */

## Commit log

2020-03-06 initial commit, added design file(wip)
2020-03-06 Adds new footprints, and BoM.
2020-03-06 Schematics, BoM updated. New project added - scale_ltc6915
2020-03-06 First commit of TPS92515 driver, ready for manufacturing
2020-03-06 Changes post gerber output in PCB file
2020-03-07 PCB Files added, for scale_hx711
2020-03-09 moved tps92515_led_driver to different repo
2020-03-09 Adds extra GPIO pins for nrf in scale_hx711
2020-03-09 updated schematic of scale_ltc6915, fixed issues
2020-03-10 BOMs, schematics updated, scale_ltc6915 PCB Design complete.
2020-03-10 DC, CS pins separated, issue fixed. In both scale_hx711 and scale_ltc6915.
2020-05-12 Add firmware for Weighing scale.
    Firmware to :
    1. Display weight on E-Paper display.
    2. Update weight in BLE advertisement.
    3. Force OTA.
    4. Characteristics according to given document.
2020-05-12 Add weighing scale board with hx711 in boards.h.
2020-05-12 Update application to use Weighing Scale Hardware.
2020-05-21 Add board file for LTC6915 board
2020-05-21 Make the checking interval every 1 ms for busy signal of e-paper
2020-05-21 Get the DFU hardware ID from board
2020-05-21 Change UUID from Batt ADC to batt percentage
2020-05-21 Update the Makefile for
    - Adding simple_adc.c for battery measurement
    - Add DFU board ID for generating the zip files
    - Remove GPIO as pin reset
2020-05-21 Weight to info display module comes in 1g format now
2020-05-21 Empty image isn't shown in refresh and info_display_show returns immediately when refreshing
2020-05-21 Few core changes
    - ms timer to start weighing is moved to weighing module
    - Added the initialization for LTC board
    - Bluetooth now can reset the tare
    - Added field for sw version
2020-05-21 BLE part has few changes like
    - Weight is sent in adv now instead of scan response
    - Weight is in int32_t format in both characteristic and adv
    - Added the controller value and sw version value in the characteristic
    - Battery percent is characteristic instead of ADC
    - Sw version is in string format now
2020-05-21 GPIO 21 isn't pin reset by default
2020-05-21 HX711 board now works with external display temporarily
2020-05-21 Weight module major changes
    - Battery value can be got in mV and percentage
    - Weight would be got in int32_t in terms of grams
    - Tare can be reset now
    - MS timer is used in weighing module now to start the initialization and measurement
    - Added proper init struct for LTC board
    - Callback from this module when weighing is done
2020-05-22 Update Info display to:
    1. Display under 1kg weight in 0.xx format.
    2. Display negative weight properly.
2020-05-29 Add DCDC enable and switching to Low Pwr on boot
2020-05-29 Add LTC driver changes
2020-05-29 Correct definintion for CLK_SRC in the board file
2021-02-04 updates Readme documentation.
2021-03-01 Updated images
2021-03-01 Adds schematic and pcb images.
2021-03-02 Updated main README with justification for design
2021-03-02 Updates sdk download link.
2021-03-02 updates images and firmware links
2021-03-03 Fixed Doxyfile. README still WIP
2021-03-04 Adds Readme files for subfolders.
2021-03-10 updated doxyfile with changes from A9 documentation
2021-03-10 Cleaned up to remove IDF files from documentation and to center the IoTReady logo in the header
2021-03-10 cleaned out old documentation files
2021-03-22 Adds open-source article
2021-03-22 minor bug fix in makefile
2021-03-24 edited article and fixed missing @param
2021-05-25 Pushing generated docs
2021-05-25 Changed title Change links to point to renamed repo
2021-05-27 adds license logo

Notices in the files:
README.md:
opensource license
